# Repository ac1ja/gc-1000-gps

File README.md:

# Firmware
Requires platformio, make

Install build deps
```
# Ubuntu/Debian
sudo apt install build-essential make

# Platformio install script, see https://docs.platformio.org/en/latest/core/installation/methods/installer-script.html
python3 -c "$(curl -fsSL https://raw.githubusercontent.com/platformio/platformio/master/scripts/get-platformio.py)"
```

Or install platformio from [here](https://platformio.org/install), this project assumes
only pio core but the ide integrations will also work

## Build

Clone and build the repo
```
git clone --recurse-submodules https://github.com/ac1ja/gc-1000-gps.git
cd firmware
make
make flash
```

Debugging notes
```
git clone --recurse-submodules https://github.com/ac1ja/gc-1000-gps.git
cd firmware
make debug
```

See docs for full instruction! https://gc-1000-gps.readthedocs.io/en/latest/

# Hardware

## Install KiCAD

Install KiCAD from [here](https://www.kicad.org/download/), find the hardware files under `hardware`

# Where is everything?

```shell
├── cad                     # CAD and design files
├── firmware                # Software and Firmware source code
└── hardware                # PCB And component design files
    └── gc-1000-gps         # GC-1000-gps board!
        └── Libraries       # External kicad libs
```

# Docs
Docs written with sphinx for use with readthedocs.
Info here https://docs.readthedocs.io/en/stable/intro/getting-started-with-sphinx.html

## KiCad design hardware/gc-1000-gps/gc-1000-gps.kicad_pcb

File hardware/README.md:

# Hardware

All the hardware for the inverted pendulum is made with (KiCAD)[https://www.kicad.org/]!

All the automation for this project is done with (KiBot)[https://github.com/INTI-CMNB/KiBot]

## Getting Started

Always clone this repo using submodules!

```shell
git clone --recurse-submodules https://github.com/ac1ja/gc-1000-gps.git
```

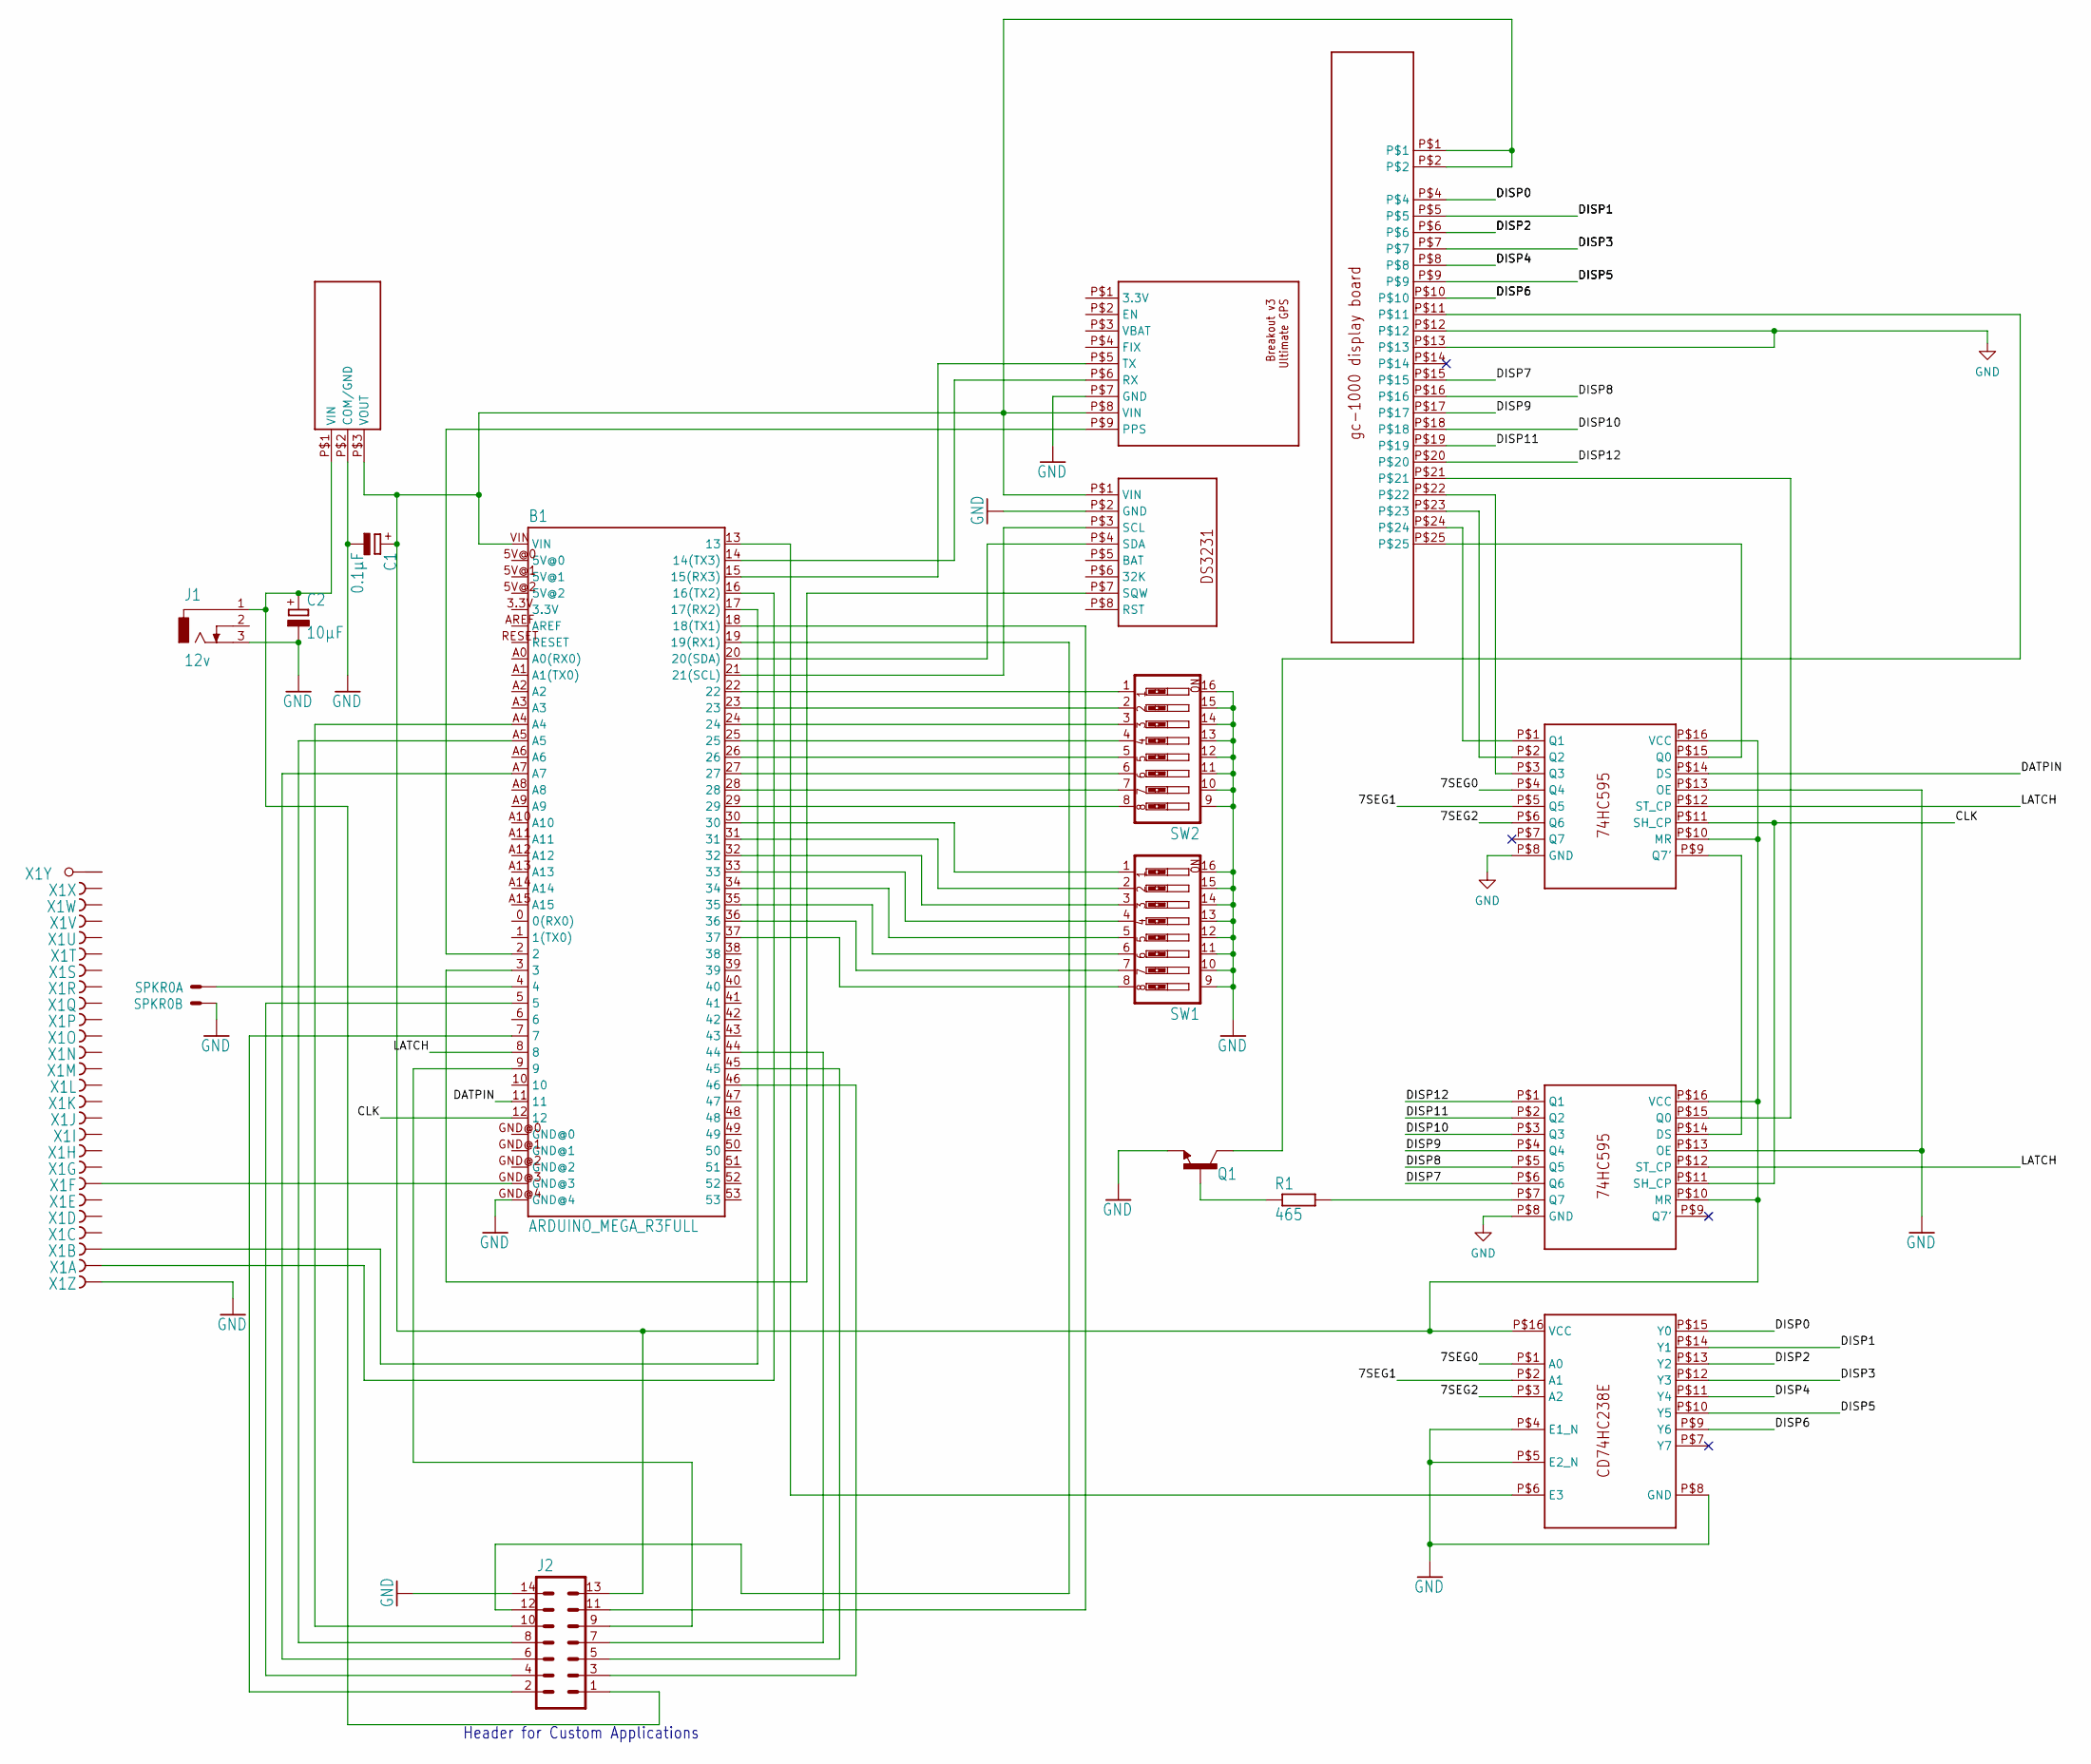
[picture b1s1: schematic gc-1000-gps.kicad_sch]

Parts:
B1: ARDUINO_MEGA_R3FULL; ARDUINO_MEGA
C1: 0.1µF; E1,8-4
C2: 10µF; E1,8-4
J1: 12v; DCJ0303
J2: MA07-2
Q1: 2N3904; TO92
R1: 465; 0207_10
SPKR0: 22-23-2021
SW1, SW2: SW_DIP-8; EDG-08
U1: OKI-78SR
U$1: PA6H-PROTO; PA6H
U$2: CD74HC238E
U$4: DS3231
U$5: GC-1000-DISP
U$6, U$7: 74HC595
X1: F25HPS; F25HP

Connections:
5VLINE: B1.VIN, C1.+, J2.13, U1.P$3 (VOUT), U$1.P$8 (VIN), U$2.P$16 (VCC), U$4.P$1 (VIN), U$5.P$1, U$5.P$2, U$6.P$10 (MR), U$6.P$16 (VCC), U$7.P$10 (MR), U$7.P$16 (VCC)
7SEG0: U$2.P$1 (A0), U$6.P$4 (Q4)
7SEG1: U$2.P$2 (A1), U$6.P$5 (Q5)
7SEG2: U$2.P$3 (A2), U$6.P$6 (Q6)
B$2: B1.21 (21(SCL)), U$4.P$3 (SCL)
CLK: B1.12, U$6.P$11 (SH_CP), U$7.P$11 (SH_CP)
CUTOUT: B1.19 (19(RX1)), J2.12
DATPIN: B1.8, U$6.P$12 (ST_CP), U$7.P$12 (ST_CP)
DISP0: U$2.P$15 (Y0), U$5.P$4
DISP1: U$2.P$14 (Y1), U$5.P$5
DISP2: U$2.P$13 (Y2), U$5.P$6
DISP3: U$2.P$12 (Y3), U$5.P$7
DISP4: U$2.P$11 (Y4), U$5.P$8
DISP5: U$2.P$10 (Y5), U$5.P$9
DISP6: U$2.P$9 (Y6), U$5.P$10
DISP7: U$5.P$15, U$7.P$6 (Q6)
DISP8: U$5.P$16, U$7.P$5 (Q5)
DISP9: U$5.P$17, U$7.P$4 (Q4)
DISP10: U$5.P$18, U$7.P$3 (Q3)
DISP11: U$5.P$19, U$7.P$2 (Q2)
DISP12: U$5.P$20, U$7.P$1 (Q1)
GND: B1.GND@4, C1.-, C2.-, J1.3, J2.14, Q1.3 (E), SPKR0.2, SW1.9, SW1.10, SW1.11, SW1.12, SW1.13, SW1.14, SW1.15, SW1.16, SW2.9, SW2.10, SW2.11, SW2.12, SW2.13, SW2.14, SW2.15, SW2.16, U1.P$2 (COM/GND), U$1.P$7 (GND), U$2.P$4 (E1_N), U$2.P$5 (E2_N), U$2.P$8 (GND), U$4.P$2 (GND), U$5.P$12, U$5.P$13, U$6.P$8 (GND), U$6.P$13 (OE), U$7.P$8 (GND), U$7.P$13 (OE), X1.1 (F)
LATCH: B1.4, SPKR0.1
unnamed: B1.3, U$4.P$7 (SQW)
unnamed: C2.+, J1.1, J2.1, U1.P$1 (VIN)
unnamed: B1.20 (20(SDA)), U$4.P$4 (SDA)
unnamed: B1.22, SW2.1
unnamed: B1.2, U$1.P$9 (PPS)
unnamed: B1.23, SW2.2
unnamed: B1.24, SW2.3
unnamed: B1.25, SW2.4
unnamed: B1.26, SW2.5
unnamed: B1.27, SW2.6
unnamed: B1.28, SW2.7
unnamed: B1.29, SW2.8
unnamed: B1.30, SW1.1
unnamed: B1.31, SW1.2
unnamed: B1.32, SW1.3
unnamed: B1.33, SW1.4
unnamed: B1.34, SW1.5
unnamed: B1.35, SW1.6
unnamed: B1.36, SW1.7
unnamed: B1.37, SW1.8
unnamed: B1.13, U$2.P$6 (E3)
unnamed: U$5.P$21, U$7.P$15 (Q0)
unnamed: Q1.2 (B), R1.1
unnamed: R1.2, U$7.P$7 (Q7)
unnamed: Q1.1 (C), U$5.P$11
unnamed: U$5.P$22, U$6.P$3 (Q3)
unnamed: U$5.P$23, U$6.P$2 (Q2)
unnamed: U$5.P$24, U$6.P$1 (Q1)
unnamed: U$5.P$25, U$6.P$15 (Q0)
unnamed: B1.16 (16(TX2)), X1.2 (F)
unnamed: B1.17 (17(RX2)), X1.3 (F)
unnamed: B1.GND@3, X1.7 (F)
unnamed: B1.14 (14(TX3)), U$1.P$6 (RX)
unnamed: B1.15 (15(RX3)), U$1.P$5 (TX)
unnamed: B1.A5, J2.8
unnamed: B1.18 (18(TX1)), J2.11
unnamed: B1.A4, J2.10
unnamed: B1.A7, J2.6
unnamed: B1.5, J2.4
unnamed: B1.7, J2.2
unnamed: B1.9, J2.9
unnamed: B1.44, J2.7
unnamed: B1.45, J2.5
unnamed: B1.46, J2.3
unnamed: U$6.P$9 (Q7'), U$7.P$14 (DS)
unnamed: B1.11, U$6.P$14 (DS)

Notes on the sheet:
Header for Custom Applications

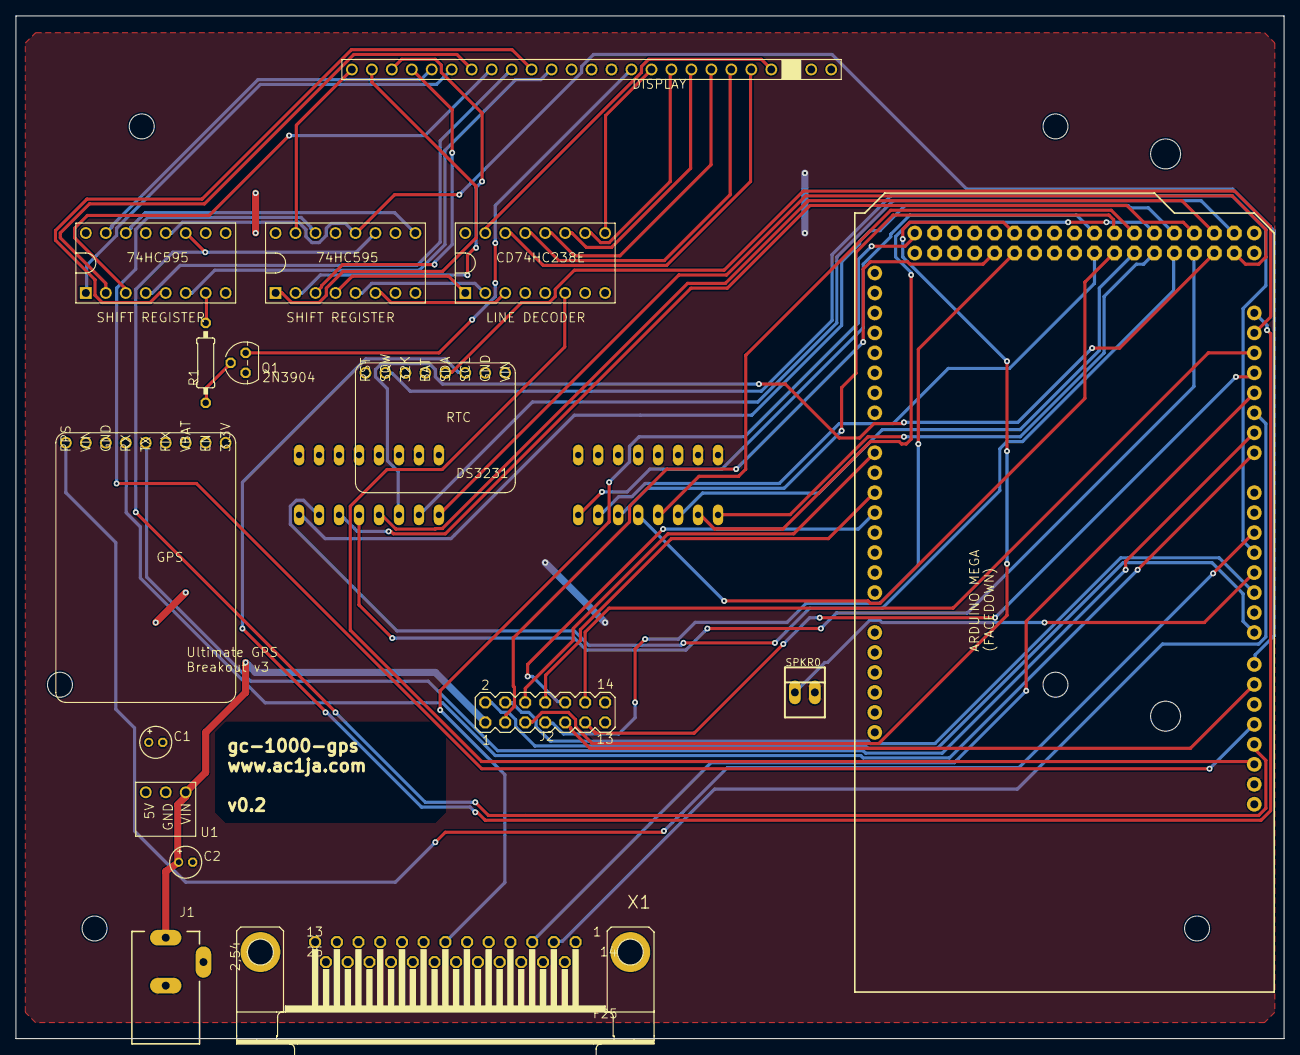
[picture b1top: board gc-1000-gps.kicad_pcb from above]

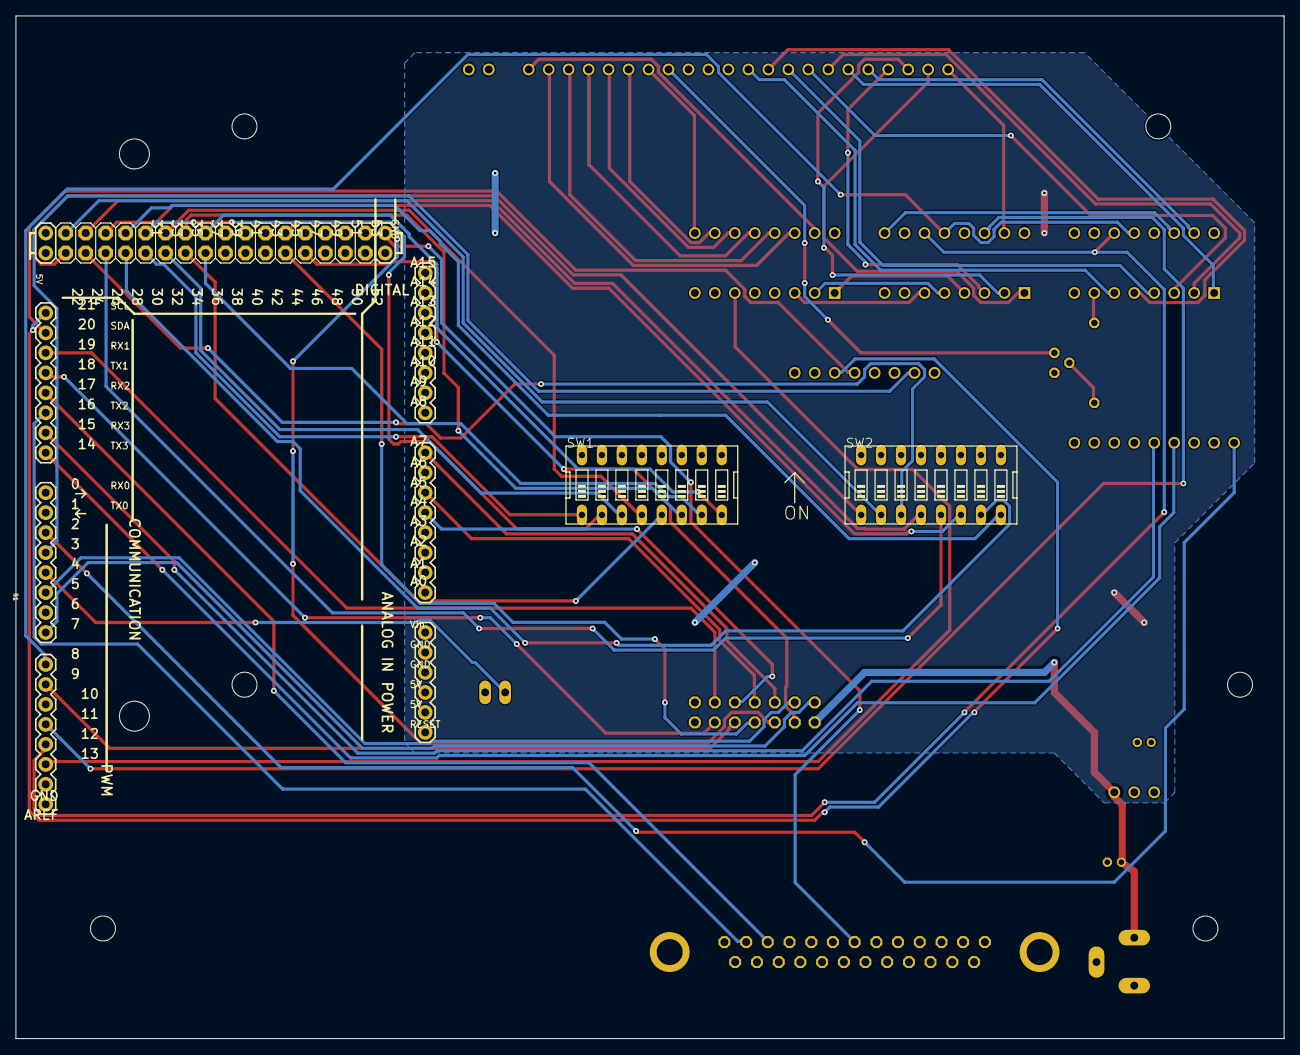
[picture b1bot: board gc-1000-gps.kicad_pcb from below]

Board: 2 copper layers, 161.3 x 130.1 mm, 26 parts (3 on the bottom side), 69 nets.

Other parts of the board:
@HOLE0, @HOLE1, @HOLE2, @HOLE3, @HOLE4, @HOLE5, @HOLE6, @HOLE7: (no value)

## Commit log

2021-11-09 Import v0.1
2021-11-09 Import v0.2
2021-11-09 Attempt git autonaming in docs
2021-11-11 Fix up auto-release naming
2021-11-11 Specify build pdf
2021-11-11 Cleanup hyperlinks and move images
2021-11-11 Rename developing to contribuiting
2021-11-11 Add reference to getting started in contribuiting
2021-11-11 Cleanup old hyperlinks and make intro a bit longer
2021-11-11 Fix dirty issue, fix blank pages
2021-11-11 Fix broken hyperlinks
2021-12-28 Create IO Shield for final release of gc-1000-gps
2021-12-30 import all images
2022-01-04 Fix missing holes in io shield
2022-01-06 Boilerplate
2022-01-06 Import all major assembly instruction changes!
2022-01-10 Fix Snug fit when inserting db25
2022-01-11 Fix incorrect picture for releases page
2022-01-11 Add better notes on contributing
2022-01-11 Actually fix typos in devel
2022-01-18 Add better docs about flashing hex
2022-01-25 Fix redundant 'for example'
2022-07-12 Ugly but compiles fine
2022-07-12 messy but it fixes the MOTD
2022-07-12 Request more of our libs
2022-07-15 This is half baked at best
2022-07-18 Some improvements
2022-07-18 include readme
2022-07-18 This works
2022-07-18 Seems to be working well
2022-07-18 Change default behavior
2022-07-19 Fixup hi-spec function
2022-07-19 in the last minute is fair
2022-07-25 Make var name more unambigous
2022-07-27 Watchdog should save us now
2022-07-28 Watchdog should work *now*
2022-07-28 Watchdog should work *now* prolly
2022-08-01 move watchdog again
2023-01-12 Retool docs for new build tool
2023-01-22 Cleanup some of the docs to prep for reivew
2023-05-11 Improve logging
2023-05-11 Clean up a little
2023-05-11 Begin the migration away from timezone
2023-05-11 Add check workflow
2023-05-11 Add badge
2023-05-11 Bump versions
2023-05-11 Switch to platformio (#3)
2023-05-11 Layout tasks
2023-05-11 Add more components to simplified code
2023-05-15 strange bug where vtaskdelay wont return
2023-05-15 Bake for freeRTOS
2023-05-15 Remove unused gitlab CI
2023-05-15 Update docs with new links
2023-05-16 Add serial debug instructions
2023-05-16 Add more serial protections (seem to possibly be causing lockup? more investigation needed)
2023-05-16 Migrate to kicad 7
2023-05-16 remove unused
2023-05-16 Skip ERC
2023-05-17 Bump kibot to 7
2023-05-17 Add requirements.txt
2023-05-17 fix reqs
2023-07-05 This does not compile (yet)
2023-07-10 change libs and simplify sync
2023-07-11 fix a drift bug
2023-07-25 Bugfix/Memory Leaks (#9)
2023-07-25 Add OS Specific instructions
2023-07-25 Bump
2023-07-25 Fix order of tabs
2023-07-25 Add url to docs
2023-07-25 Patch issue compiling on windows
2023-07-25 Make build flags more portable
2023-08-07 Migrate to kicad 7 (#7)
2023-08-09 Add graphs and begin getting started
2023-08-09 upgrade sequence diagram
2023-08-09 ISRPPS functioning
2023-08-09 Clean some constants and make space for future migrations
2023-08-14 Add BOM generator
2024-04-15 old bump
2024-04-15 Scan dip switches faster
2024-04-15 Quick load RTC time at boot
2024-04-16 misc improvements
2024-04-16 Enable no-sync flash
2024-04-23 Patch up everything
2024-10-31 RTC Refactor (#10)
    This was the latest build of the code and we'll be merging ontop of this later
2024-10-31 button up last testing infrastructure
2024-10-31 fix backend
2024-10-31 Finish integration
2024-10-31 Flatten main.cpp
2024-10-31 Flatten main.cpp (again)
2024-10-31 Move changes back in
2024-10-31 bump RTC lib
2024-10-31 bump AVR debugger
2024-10-31 Fix in review
2024-10-31 Fix test_time and comments
2024-10-31 Condense review from today
2024-11-08 Edit tests
2024-11-08 leave on bench with this ver
2024-12-07 RTC Rollover Fix (#12)
    Changed the base from main to v0.3_RC, mainly did this to squash all these changes into a neat package (Most are reviewed anyway)
    Makes it easier to track in future code review
    Places all RC ready code in one spot
2024-12-07 Fix edit on github link
2024-12-07 Try READTHEDOCS_GIT_IDENTIFIER instead
2024-12-10 Bump PIO versions
2024-12-10 Bump build uses
2024-12-10 Potential fix for #18
    Implements some basic _start/duration checking for main loop and gps cracking
    only updates internal time if drift with gpsSecond (can be merged with RTC second)
2024-12-10 Bump hiSpecMax Age
2024-12-10 Add code and comment improvements
2024-12-10 Fix some spelling errors
2024-12-10 Fix for #18, hanging at top of minute (#19)
    fix for #18
2024-12-24 Fix regression causing #20 Closes #20
    Co-Authored By: @nsoggu
2024-12-24 Dont display leading zeros when NOT in 24hr mode
2025-01-02 Patch for #16
2025-01-03 Apply patch for #16 from @nsoggu
    Co-Authored By: @nsoggu
2025-11-14 Seems to fix the tickover bug but has some glitchyness pre-sync
